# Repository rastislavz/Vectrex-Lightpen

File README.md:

# Vectrex lightpen with integrated buttons

# The construction details

The building of this lightpen is a bit tedious process since it uses the refillable whiteboard marker (PILOT V-Board Master 5979) instead some genuine build body.
The first step is to disembowel the marker guts: after the back is screwed open and the ink cartridge is taken out, the rest of the guts can be simply pulled out with the long nose pliers.
The next step is drilling the holes for cable and for 4 microswitch buttons. To drill the button holes precisely, i found the best way is to first apply the label with the precut button holes and to drill the holes after the label is applied. Since I had lots of labels made for the ordinary lightpen without precut holes, I have made the drill template (in svg directory) which I have printed out, overlaid with the label and than punched the holes with the leather holes puncher.

The cables are directly soldered into the PCBs. Both PCBs are designed with the holes for the cables which serves as strain relife when cables are threaded through the holes. The main body (or call it the lightpen box) PCB contains also smaller holes by which cables can be additionaly secured by cable ties.

The PCB with the microswitches and phototransistor has to be secure inside the pen with some piece of plastic/thick paper and glue.

Its quite interesting where I have found the plastic 9pin connector with 90° pins I have used in building the pen: when I needed 9pin cables for some Vectrex controllers I have used Sega etension cables and I have cut off the male part, and some of those had a small bump on it (like the one sold by console5 https://console5.com/store/atari-sega-commodore-6-1-8m-joystick-controller-extension-cable-cord.html). I was curious why that bump is there and when I have cracked it open, I have found out that Chinese have used the 90° PCB connectors for making the cable and they have just soldered wires onto the pins, but then they had to make that bump to fit. So you do not have to buy that connector if you are using the same cables for the build.

The box case is made with 2 laser cut acrilic (or whatewer material) sheet: in the svg folder.

Shield: [![CC BY-SA 4.0][cc-by-sa-shield]][cc-by-sa]

This work is licensed under a
[Creative Commons Attribution-ShareAlike 4.0 International License][cc-by-sa].

[![CC BY-SA 4.0][cc-by-sa-image]][cc-by-sa]

[cc-by-sa]: http://creativecommons.org/licenses/by-sa/4.0/
[cc-by-sa-image]: https://licensebuttons.net/l/by-sa/4.0/88x31.png
[cc-by-sa-shield]: https://img.shields.io/badge/License-CC%20BY--SA%204.0-lightgrey.svg

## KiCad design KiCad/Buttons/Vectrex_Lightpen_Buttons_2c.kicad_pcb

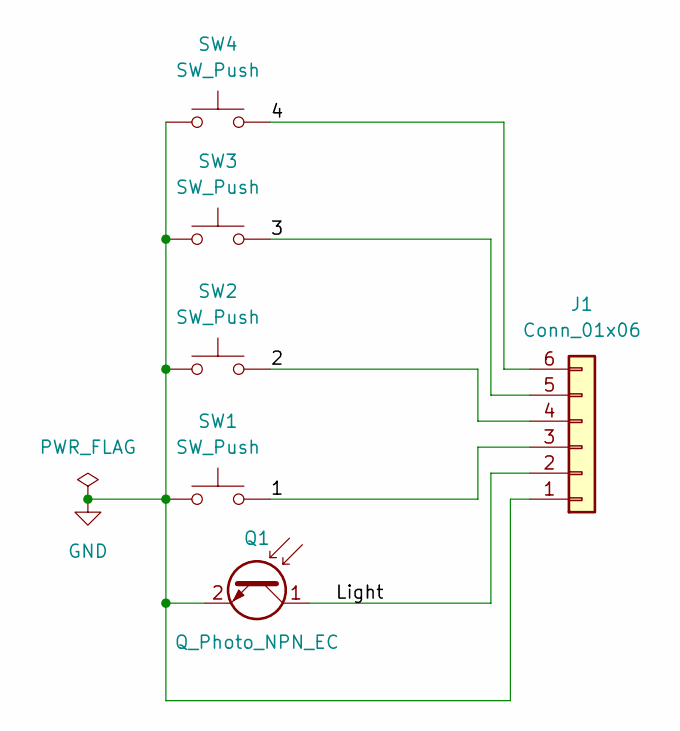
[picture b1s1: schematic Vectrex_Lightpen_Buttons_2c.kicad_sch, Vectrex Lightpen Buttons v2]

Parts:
J1: Conn_01x06; SoldeWire_1x06_P2.00mm_ZigZag
Q1: Q_Photo_NPN_EC; LED_D3.0mm_Clear
SW1, SW2, SW3, SW4: SW_Push; SW_PUSH_6mm_H7.3mm

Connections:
/1: J1.3, SW1.2
/2: J1.4, SW2.2
/3: J1.5, SW3.2
/4: J1.6, SW4.2
/Light: J1.2, Q1.1 (C)
GND: J1.1, Q1.2 (E), SW1.1, SW2.1, SW3.1, SW4.1

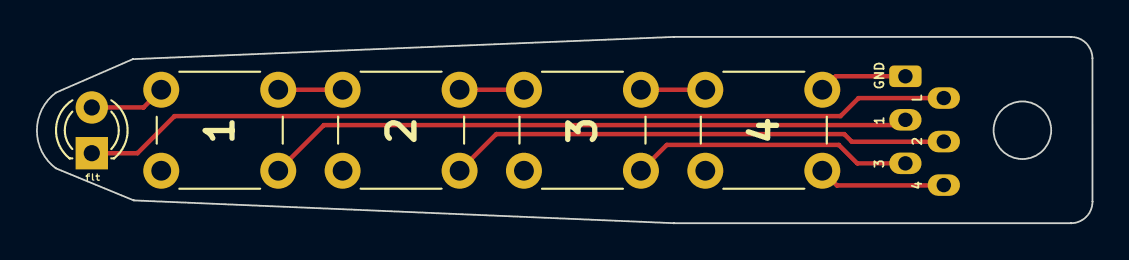
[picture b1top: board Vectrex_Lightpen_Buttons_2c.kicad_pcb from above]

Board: 2 copper layers, 58.6 x 10.4 mm, 6 parts (0 on the bottom side), 6 nets.

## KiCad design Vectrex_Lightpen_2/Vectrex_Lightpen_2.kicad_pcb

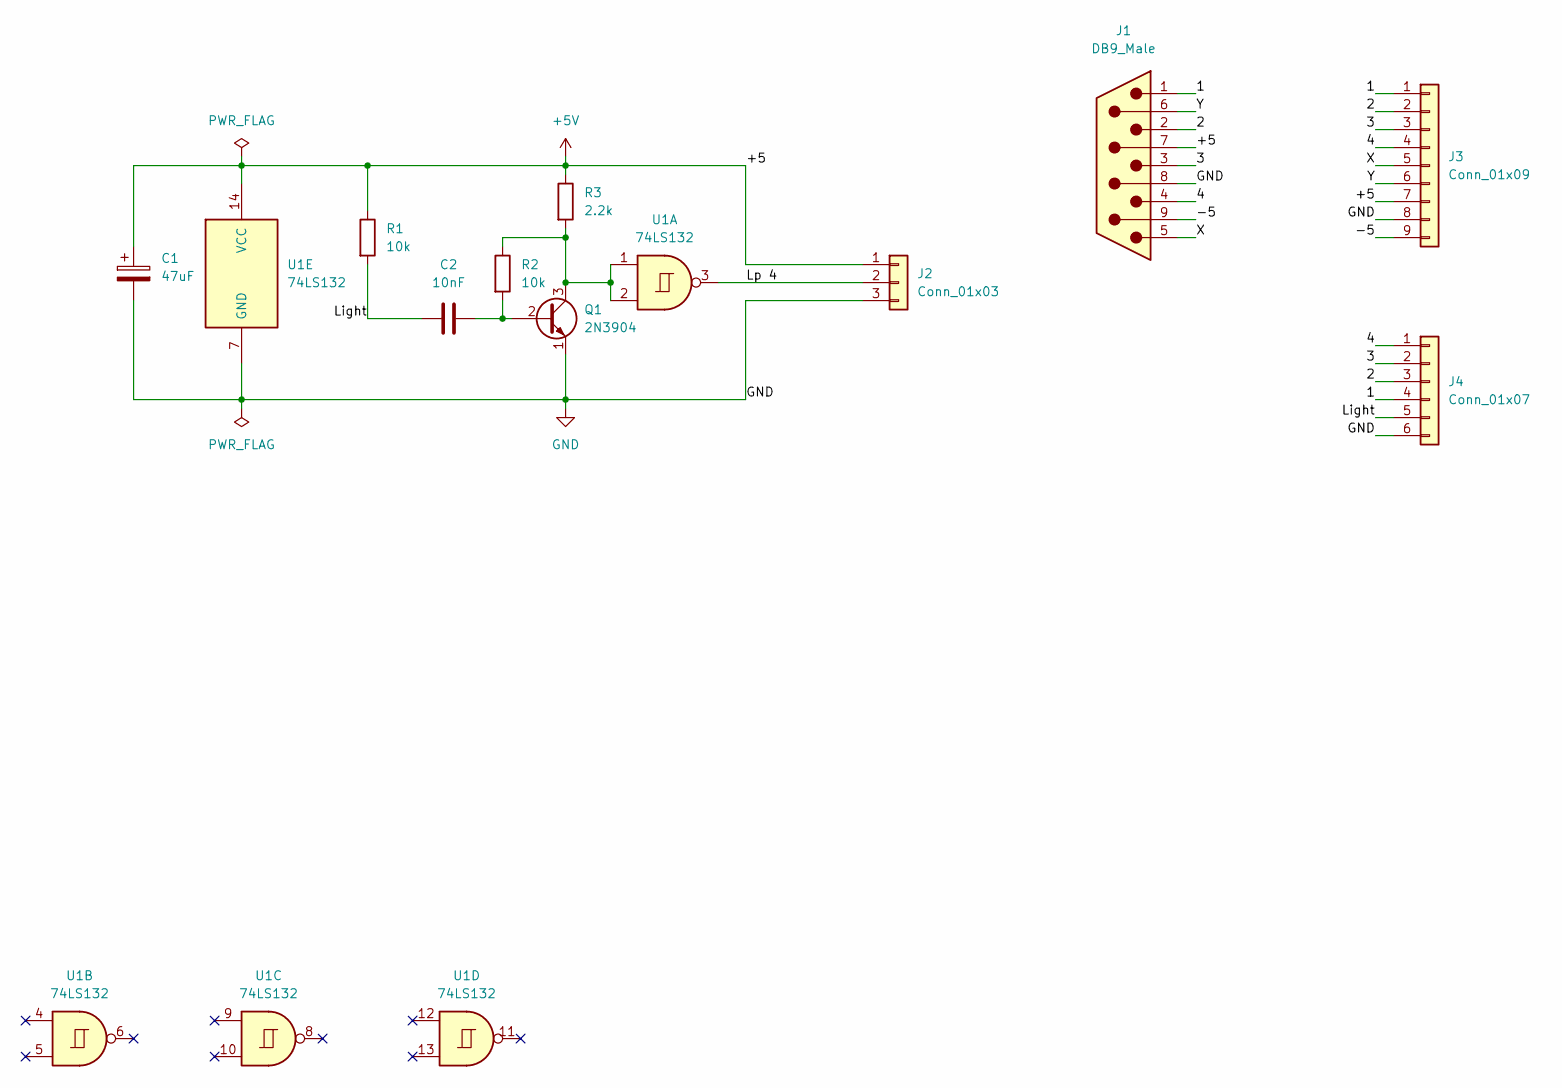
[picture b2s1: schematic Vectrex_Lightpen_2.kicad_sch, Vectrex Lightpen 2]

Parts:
C1: 47uF; CP_Radial_D5.0mm_P2.00mm
C2: 10nF; C_Disc_D3.0mm_W2.0mm_P2.50mm
J1: DB9_Male; DSUB-9_Male_Horizontal_Sega_Joystick
J2: Conn_01x03; SolderWire-0.1sqmm_1x03_P3mm_D0.4mm_OD1mm
J3: Conn_01x09; DSUB-9_solderwire
J4: Conn_01x07; SoldeWire_1x06_P2.00mm_Vertical
Q1: 2N3904; TO-92_Inline
R1, R2: 10k; R_Axial_DIN0204_L3.6mm_D1.6mm_P5.08mm_Horizontal
R3: 2.2k; R_Axial_DIN0204_L3.6mm_D1.6mm_P5.08mm_Horizontal
U1: 74LS132; DIP-14_W7.62mm

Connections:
+5V: C1.1, J1.7, J2.1, J3.7, R1.1, R3.1, U1.14 (VCC)
/1: J1.1, J3.1, J4.4
/2: J1.2, J3.2, J4.3
/3: J1.3, J3.3, J4.2
/4: J1.4, J3.4, J4.1
/-5: J1.9, J3.9
/Light: C2.1, J4.5, R1.2
/Lp 4: J2.2, U1.3
/X: J1.5, J3.5
/Y: J1.6, J3.6
GND: C1.2, J1.8, J2.3, J3.8, J4.6, Q1.1 (E), U1.7 (GND)
unnamed: C2.2, Q1.2 (B), R2.2
unnamed: Q1.3 (C), R2.1, R3.2, U1.1, U1.2

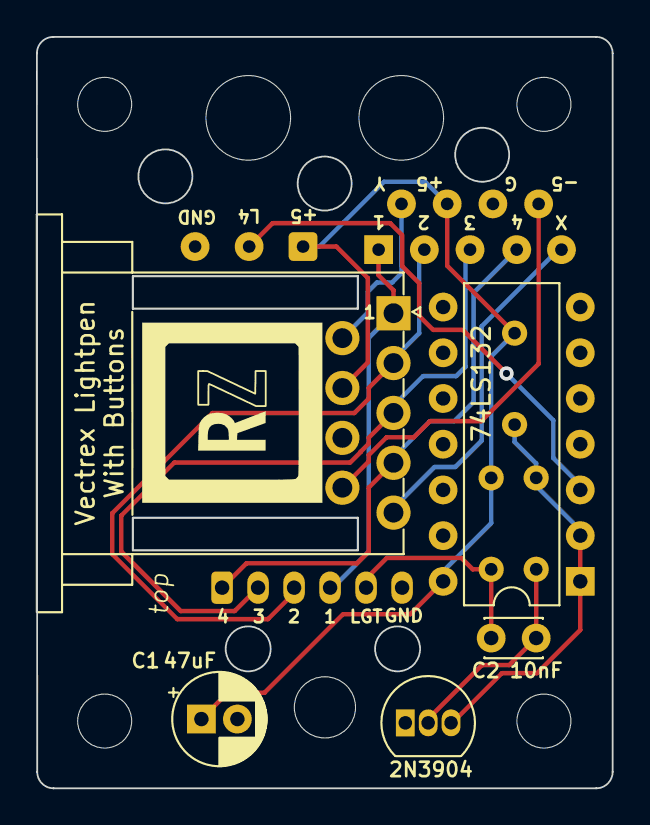
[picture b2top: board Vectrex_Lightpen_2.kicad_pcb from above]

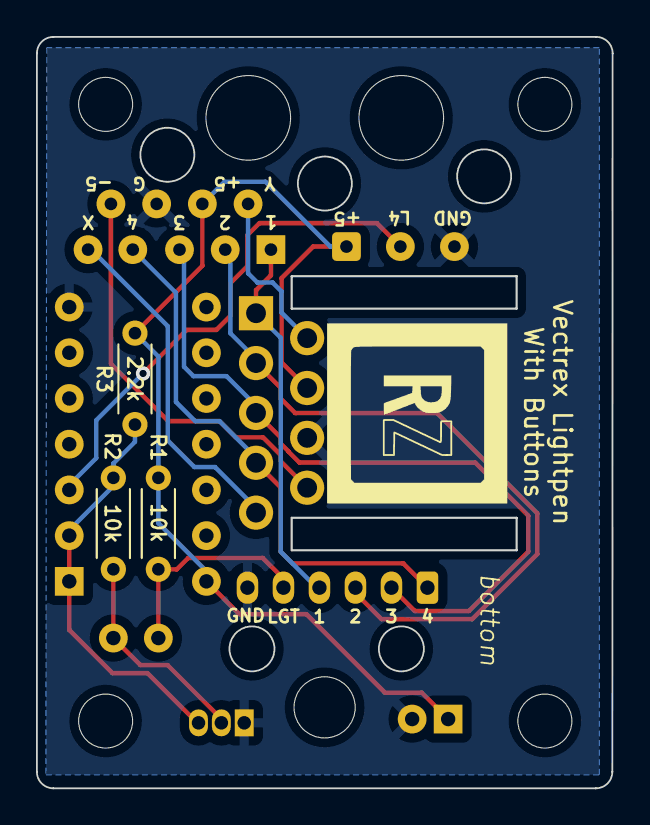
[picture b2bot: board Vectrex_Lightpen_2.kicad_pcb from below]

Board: 2 copper layers, 32.0 x 41.7 mm, 19 parts (4 on the bottom side), 13 nets.

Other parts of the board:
F1: LOGO; RZ_10mm_inverted
FB: LOGO; RZ_10mm_inverted
REF1, REF2, REF3, REF6: MH 2.5mm; MountingHole_2.5mm
REF5, REF7: MountingHole_4.5mm

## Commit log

2023-10-17 Renamed KiCad directory
2023-10-17 Added svg
2023-10-22 Added lightpen buttons pcb KiCad, images
2023-10-22 Added images of finished lightpen
2023-10-23 Added license
2023-10-23 Added license file
2023-11-14 Export to some other file types
